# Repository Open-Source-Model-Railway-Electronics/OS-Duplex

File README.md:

# OS-Duplex

The OS-Duplex is a dual DCC accessory decoder designed for all types of turnout drives — from traditional solenoids to motor drives and relay modules for frog polarization.  
Each side (A and B) can operate independently or be linked together.

Optional relay sockets allow you to add point frog polarization, or use the same outputs to drive extra coils or motors.

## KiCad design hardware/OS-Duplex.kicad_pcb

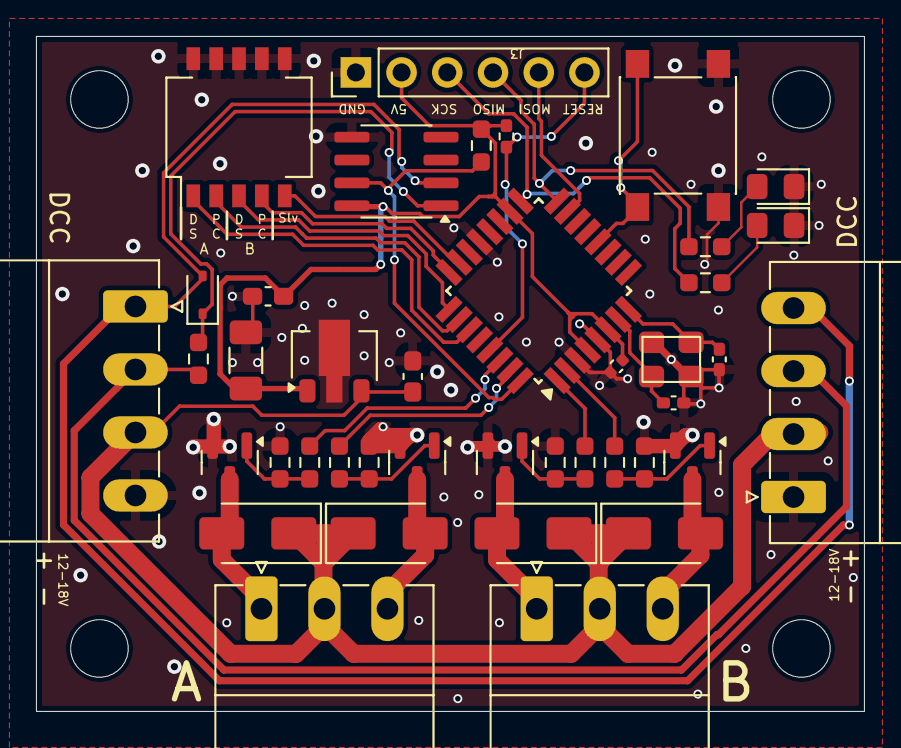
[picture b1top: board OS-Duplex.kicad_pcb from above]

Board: 2 copper layers, 46.0 x 37.5 mm, 41 parts (0 on the bottom side), 33 nets.

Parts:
C1, C2: 12pF; C_0402_1005Metric_Pad0.74x0.62mm_HandSolder
C3: 100nF; C_0402_1005Metric
C301: 330nF; C_0603_1608Metric_Pad1.08x0.95mm_HandSolder
C302: 100nF; C_0603_1608Metric_Pad1.08x0.95mm_HandSolder
C303: 100uF; C_1206_3216Metric_Pad1.33x1.80mm_HandSolder
D1: D; D_SOD-323
D2, D4: LED; LED_0805_2012Metric_Pad1.15x1.40mm_HandSolder
D11, D21: SS34; D_SMA
D12, D22: D_SMA
J3: ICSP; PinHeader_1x06_P2.54mm_Vertical
J11, J21: PhoenixContact_MC_1,5_3-G-3.5_1x03_P3.50mm_Horizontal
J62, J63: Screw_Terminal_01x04; PhoenixContact_MC_1,5_4-G-3.5_1x04_P3.50mm_Horizontal
Q11, Q12, Q21, Q22: AO3400A; SOT-23
R1, R801: 10k; R_0603_smalltext
R2: 10k; R_0402_1005Metric_Pad0.72x0.64mm_HandSolder
R5: 1k5; R_0603_smalltext
R6: 6k2; R_0603_1608Metric_Pad0.98x0.95mm_HandSolder
R11, R12, R21, R22: 22R; R_0603_1608Metric_Pad0.98x0.95mm_HandSolder
R13, R14, R23, R24: 10k; R_0603_1608Metric_Pad0.98x0.95mm_HandSolder
SW1: SW_SPST; tactile_SMD_6mm
SW901: SW_DIP_x05; SW_DIP_SPSTx05_Slide_KingTek_DSHP05TS_W7.62mm_P1.27mm
U21: L78L05_SOT89; SOT-89-3
U101: ATmega328-A; TQFP-32_7x7mm_P0.8mm
U801: HCPL-0631; SOIC-8_3.9x4.9mm_P1.27mm
Y1: Crystal_GND2; crystal_arduino

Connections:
+5V: C3.1, C302.1, C303.1, J3.2, R2.1, R801.1, U21.1 (OUT), U101.4 (VCC), U101.6 (VCC), U101.18 (AVCC), U801.8 (VCC)
/DCC/A: D1.2 (A), J62.1, J63.4, U801.2 (C1)
/DCC/B: J62.2, J63.3, R5.1
/DCC/DCC_TTL: R801.2, U101.32 (PD2), U801.7 (VO1)
/atmega/1.A: R12.1, U101.2 (PD4)
/atmega/1.B: R11.1, U101.1 (PD3)
/atmega/2.A: R22.1, U101.31 (PD1)
/atmega/2.B: R21.1, U101.30 (PD0)
/atmega/LED: J3.3, R6.1, U101.17 (PB5)
/atmega/LED_BLUE: J3.4, R1.1, U101.16 (PB4)
/atmega/MOSI: J3.5, U101.15 (PB3)
/atmega/RESET: J3.6, R2.2, U101.29 (~RESET/PC6)
/atmega/X1: C1.2, U101.7 (XTAL1/PB6), Y1.1
/atmega/X2: C2.2, U101.8 (XTAL2/PB7), Y1.3
/atmega/dipSw1: SW901.5, U101.23 (PC0)
/atmega/dipSw2: SW901.4, U101.24 (PC1)
/atmega/dipSw3: SW901.3, U101.25 (PC2)
/atmega/dipSw4: SW901.2, U101.26 (PC3)
/atmega/dipSw5: SW901.1, U101.27 (PC4)
GND: C1.1, C2.1, C3.2, C301.2, C302.2, C303.2, D2.1 (K), D4.1 (K), J3.1, J62.4, J63.1, Q11.2 (S), Q12.2 (S), Q21.2 (S), Q22.2 (S), R13.1, R14.1, R23.1, R24.1, SW1.2 (B), SW901.6, SW901.7, SW901.8, SW901.9, SW901.10, U21.2 (GND), U101.3 (GND), U101.5 (GND), U101.21 (GND), U801.5 (GND), Y1.2 (GND), Y1.4 (GND)
unnamed: D1.1 (K), R5.2, U801.1 (A1)
unnamed: D2.2 (A), R1.2
unnamed: D4.2 (A), R6.2
unnamed: D11.2 (A), J11.1, Q11.3 (D)
unnamed: D12.2 (A), J11.3, Q12.3 (D)
unnamed: D21.2 (A), J21.1, Q21.3 (D)
unnamed: D22.2 (A), J21.3, Q22.3 (D)
unnamed: Q11.1 (G), R11.2, R13.2
unnamed: Q12.1 (G), R12.2, R14.2
unnamed: Q21.1 (G), R21.2, R23.2
unnamed: Q22.1 (G), R22.2, R24.2
unnamed: SW1.1 (A), U101.12 (PB0)
VCC: C301.1, D11.1 (K), D12.1 (K), D21.1 (K), D22.1 (K), J11.2, J21.2, J62.3, J63.2, U21.3 (IN)

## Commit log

2025-10-27 added all files
2025-10-27 updated manual
2025-11-09 updated manual to markdown
2025-11-13 added picture
2025-11-14 changed LDO
2025-11-15 upadted readme
2026-05-24 added translations
2026-05-25 changed board file
